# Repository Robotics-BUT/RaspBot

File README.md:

KAMBot Robotic platform
========================

This repository holds all development on RaspBot robotic project.

This repository is intended to be extended by students during their
work on semestral/bachelor and Diploma theses.

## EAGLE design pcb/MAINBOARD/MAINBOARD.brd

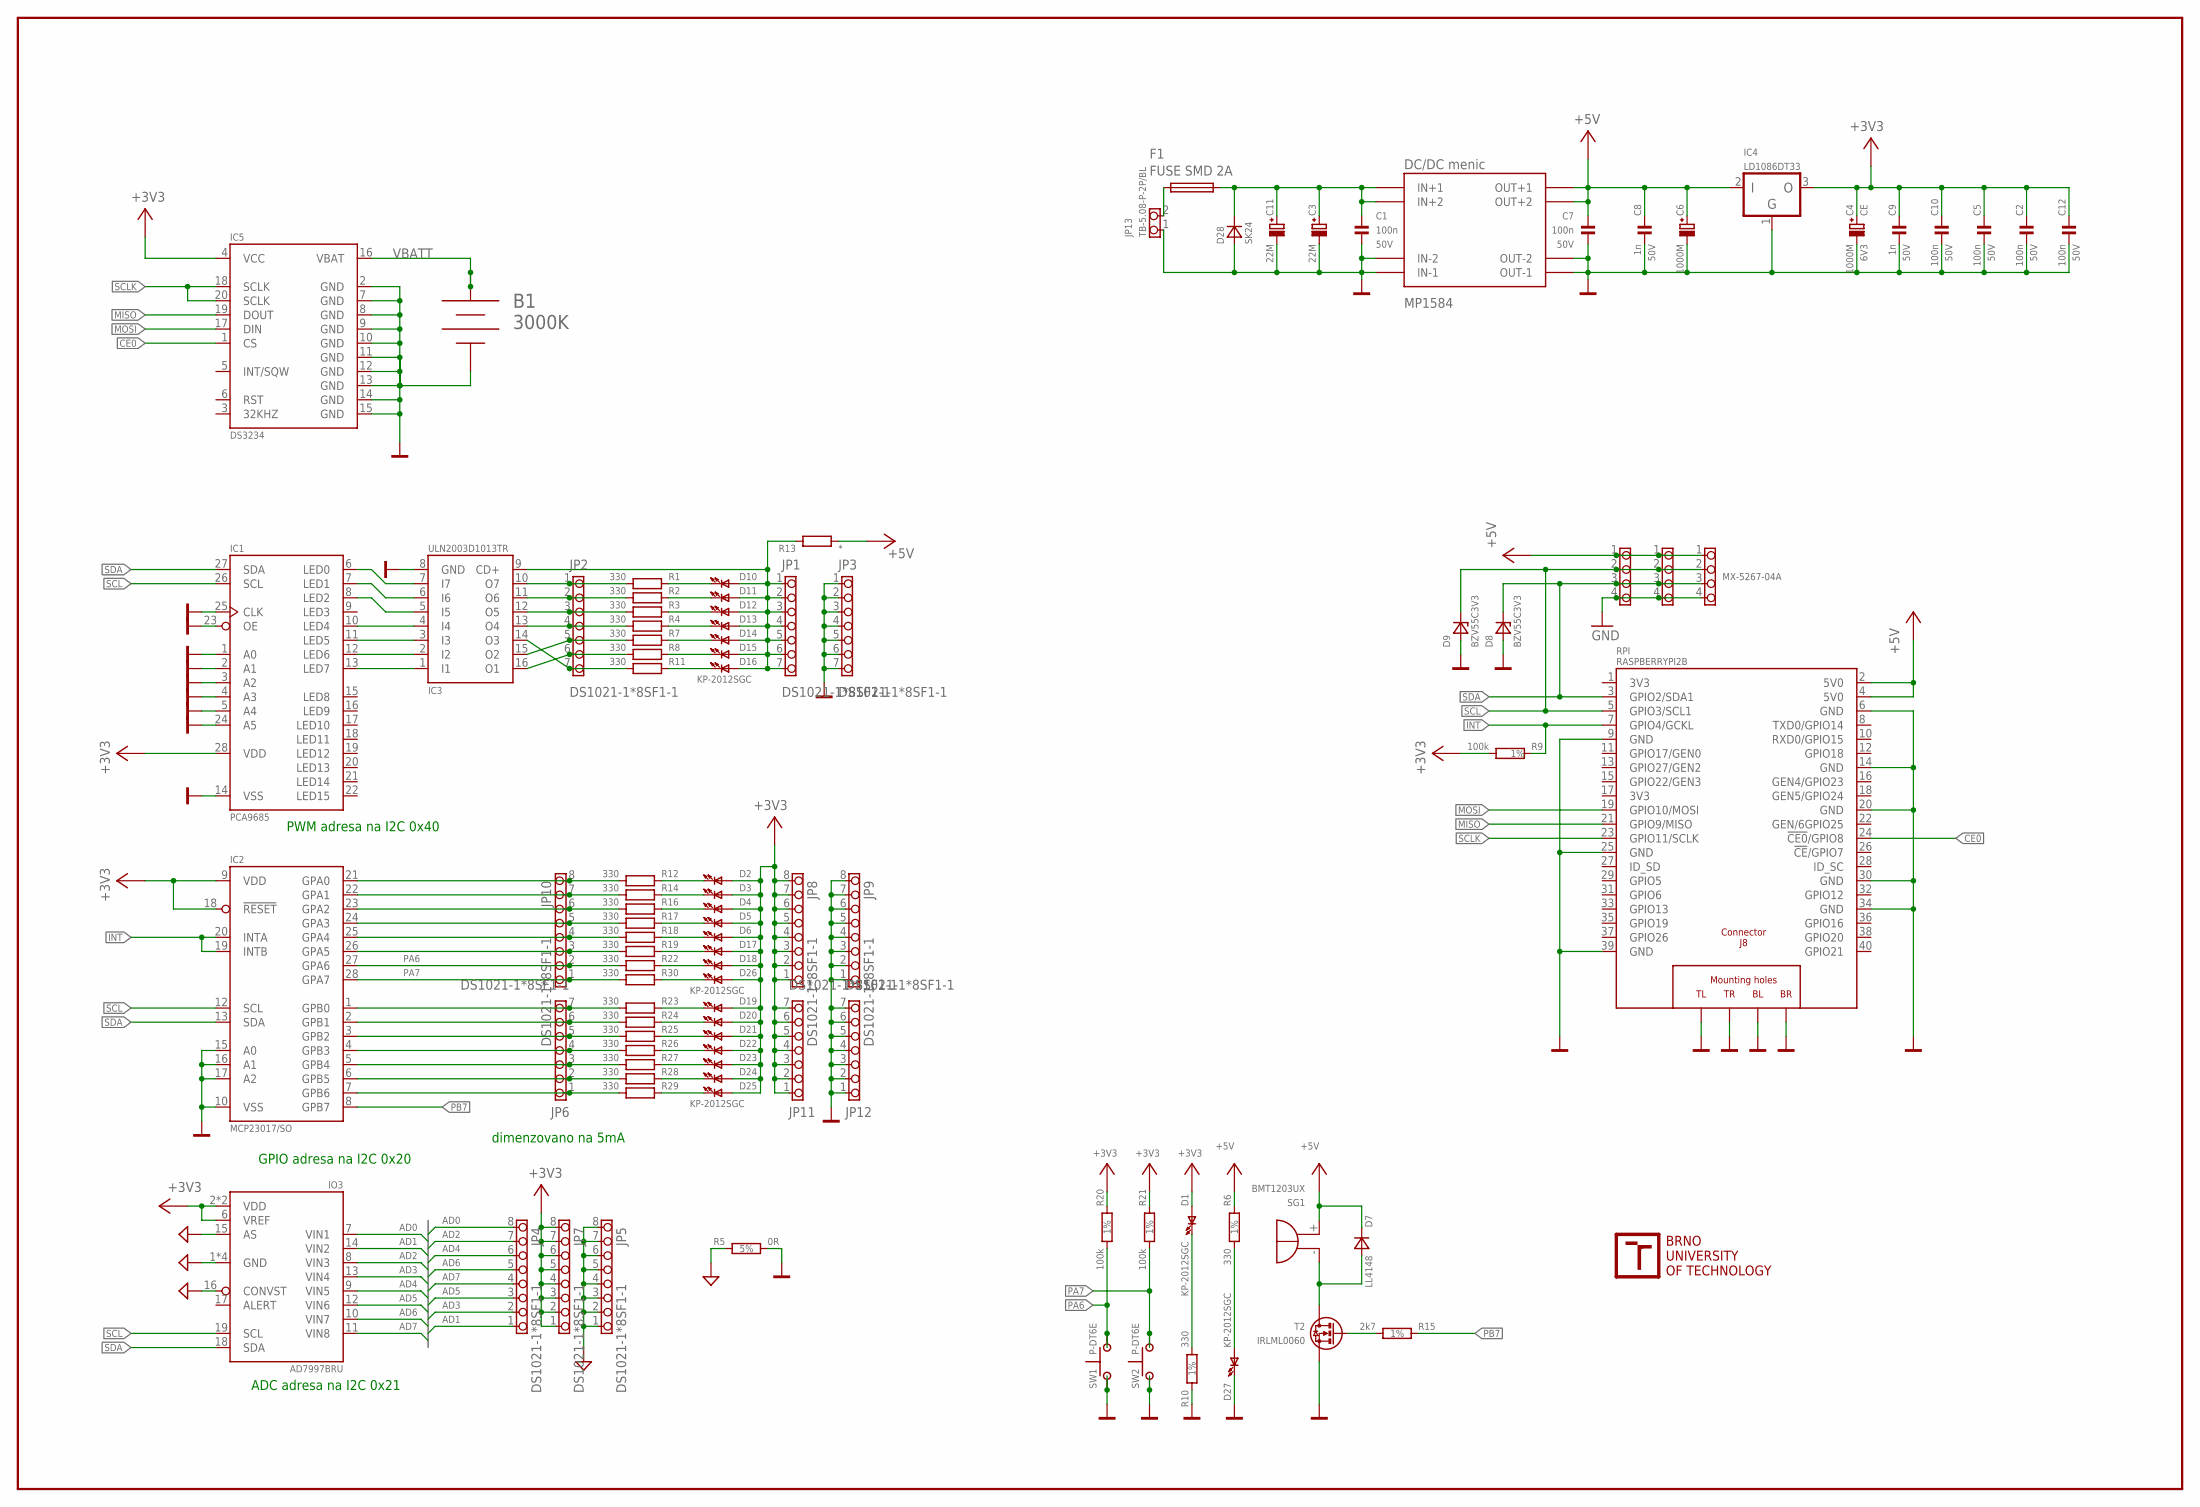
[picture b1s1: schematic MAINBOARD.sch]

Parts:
B1: 3000K
C1, C2, C5, C7, C10, C12: 100n; 0805; VOLTAGE 50V
C3, C11: 22M; CT7343D; VOLTAGE 25V
C4: 1000M; CE_D10L13_L; VOLTAGE 6V3
C6: 1000M; CE_D10L13_R; VOLTAGE 6V3
C8, C9: 1n; 0805; VOLTAGE 50V
D1, D2, D3, D4, D5, D6, D10, D11, D12, D13, D14, D15, D16, D17, D18, D19, D20, D21, D22, D23, D24, D25, D26, D27: KP-2012SGC; LED_0805
D7: LL4148; D_SOD80
D8, D9: BZV55C3V3; D_SOD80
D28: SK24; D_SMB
DC1: MP1584; DC-DC-STEP-DOWN-MALEJ
F1: FUSE SMD 2A; FUSE_SMD
IC1: PCA9685; TSSOP28
IC2: MCP23017/SO; SO28W
IC3: ULN2003D1013TR; SO16
IC4: LD1086DT33; TO252
IC5: DS3234; SO20W
IO3: AD7997BRU; TSSOP20
JP1, JP2, JP3, JP6, JP11, JP12: DS1021-1*8SF1-1; 1X07_254_M
JP4, JP5, JP7, JP8, JP9, JP10: DS1021-1*8SF1-1; 1X08_254_M
JP13: TB-5.08-P-2P/BL; 1X02_508_SROUB
JP19, JP25, JP26: MX-5267-04A; 1X04_250_MX5267
R1, R2, R3, R4, R7, R8, R11, R12, R14, R16, R17, R18, R19, R22, R23, R24, R25, R26, R27, R28, R29, R30: 330; 0805
R5: 0R; 1206; TOLERANCE 5%
R6, R10: 330; 0805; TOLERANCE 1%
R9, R20, R21: 100k; 0805; TOLERANCE 1%
R13: *; 0805
R15: 2k7; 0805; TOLERANCE 1%
RPI: RASPBERRYPI2B; RASPBERRYPI2
SG1: BMT1203UX; BMT1205XH7.5
SW1, SW2: P-DT6E; P-DTE6
T2: IRLML0060; SOT23

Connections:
+3V3: C2.1, C4.P (+), C5.1, C9.2, C10.2, C12.1, D1.A, D2.A, D3.A, D4.A, D5.A, D6.A, D17.A, D18.A, D19.A, D20.A, D21.A, D22.A, D23.A, D24.A, D25.A, D26.A, IC1.28 (VDD), IC2.9 (VDD), IC2.18 (!RESET), IC4.3 (OUT), IC5.4 (VCC), IO3.2 (VDD), IO3.5 (VDD), IO3.6 (VREF), JP7.1, JP7.2, JP7.3, JP7.4, JP7.5, JP7.6, JP7.7, JP7.8, JP8.1, JP8.2, JP8.3, JP8.4, JP8.5, JP8.6, JP8.7, JP8.8, JP11.1, JP11.2, JP11.3, JP11.4, JP11.5, JP11.6, JP11.7, R9.1, R20.2, R21.2
+5V: C6.P (+), C7.1, C8.1, D7.C (K), DC1.OUT1+ (OUT+1), DC1.OUT2+ (OUT+2), IC4.2 (IN), JP19.1, JP25.1, JP26.1, R6.2, R13.1, RPI.2 (5V0), RPI.4 (5V0), SG1.+
AD0: IO3.7 (VIN1), JP4.8
AD1: IO3.14 (VIN2), JP4.1
AD2: IO3.8 (VIN3), JP4.7
AD3: IO3.13 (VIN4), JP4.2
AD4: IO3.9 (VIN5), JP4.6
AD5: IO3.12 (VIN6), JP4.3
AD6: IO3.10 (VIN7), JP4.5
AD7: IO3.11 (VIN8), JP4.4
AGND: IO3.1 (GND), IO3.3 (GND), IO3.4 (GND), IO3.15 (AS), IO3.16 (CONVST), IO3.20 (GND), JP5.1, JP5.2, JP5.3, JP5.4, JP5.5, JP5.6, JP5.7, JP5.8, R5.2
B: R15.2, T2.1 (G)
C: D7.A, SG1.-, T2.2 (D)
CE0: IC5.1 (CS), RPI.24 (!CE0!/GPIO8)
GND: B1.-, C1.2, C2.2, C3.-, C4.M (-), C5.2, C6.M (-), C7.2, C8.2, C9.1, C10.1, C11.-, C12.2, D8.A, D9.A, D27.K (C), D28.A, DC1.IN1- (IN-1), DC1.IN2- (IN-2), DC1.OUT-1, DC1.OUT-2, IC1.1 (A0), IC1.2 (A1), IC1.3 (A2), IC1.4 (A3), IC1.5 (A4), IC1.14 (VSS), IC1.23 (OE), IC1.24 (A5), IC1.25 (CLK), IC2.10 (VSS), IC2.15 (A0), IC2.16 (A1), IC2.17 (A2), IC3.8 (GND), IC4.1 (GND), IC5.2 (GND), IC5.7 (GND), IC5.8 (GND), IC5.9 (GND), IC5.10 (GND), IC5.11 (GND), IC5.12 (GND), IC5.13 (GND), IC5.14 (GND), IC5.15 (GND), JP3.1, JP3.2, JP3.3, JP3.4, JP3.5, JP3.6, JP3.7, JP9.1, JP9.2, JP9.3, JP9.4, JP9.5, JP9.6, JP9.7, JP9.8, JP12.1, JP12.2, JP12.3, JP12.4, JP12.5, JP12.6, JP12.7, JP13.1, JP19.4, JP25.4, JP26.4, R5.1, R10.1, RPI.6 (GND), RPI.9 (GND), RPI.14 (GND), RPI.20 (GND), RPI.25 (GND), RPI.30 (GND), RPI.34 (GND), RPI.39 (GND), RPI.PE_BL (BL), RPI.PE_BR (BR), RPI.PE_TL (TL), RPI.PE_TR (TR), SW1.1, SW1.1A (3), SW2.1, SW2.1A (3), T2.3 (S)
INT: IC2.19 (INTB), IC2.20 (INTA), R9.2, RPI.7 (GPIO4/GCKL)
LED0: IC1.6 (LED0), IC3.7 (I7)
MISO: IC5.19 (DOUT), RPI.21 (GPIO9/MISO)
MOSI: IC5.17 (DIN), RPI.19 (GPIO10/MOSI)
unnamed: D26.K (C), R30.2
unnamed: D2.K (C), R12.2
unnamed: D18.K (C), R22.2
unnamed: D17.K (C), R19.2
unnamed: D6.K (C), R18.2
unnamed: D27.A, R6.1
unnamed: C1.1, C3.+, C11.+, D28.K, DC1.IN+1, DC1.IN+2, F1.2
unnamed: F1.1, JP13.2
unnamed: IC1.7 (LED1), IC3.6 (I6)
unnamed: D10.A, D11.A, D12.A, D13.A, D14.A, D15.A, D16.A, IC3.9 (CD+), JP1.1, JP1.2, JP1.3, JP1.4, JP1.5, JP1.6, JP1.7, R13.2
unnamed: IC1.8 (LED2), IC3.5 (I5)
unnamed: D10.K (C), R1.2
unnamed: D16.K (C), R11.2
unnamed: D1.K (C), R10.2
unnamed: IC1.10 (LED4), IC3.4 (I4)
unnamed: IC1.11 (LED5), IC3.3 (I3)
unnamed: IC1.12 (LED6), IC3.2 (I2)
unnamed: IC1.13 (LED7), IC3.1 (I1)
unnamed: D15.K (C), R8.2
unnamed: D14.K (C), R7.2
unnamed: D13.K (C), R4.2
unnamed: D12.K (C), R3.2
unnamed: D11.K (C), R2.2
unnamed: D5.K (C), R17.2
unnamed: D4.K (C), R16.2
unnamed: D3.K (C), R14.2
unnamed: D19.K (C), R23.2
unnamed: D25.K (C), R29.2
unnamed: D24.K (C), R28.2
unnamed: D23.K (C), R27.2
unnamed: D22.K (C), R26.2
unnamed: D21.K (C), R25.2
unnamed: D20.K (C), R24.2
PA0: IC2.21 (GPA0), JP10.8, R12.1
PA1: IC2.22 (GPA1), JP10.7, R14.1
PA2: IC2.23 (GPA2), JP10.6, R16.1
PA3: IC2.24 (GPA3), JP10.5, R17.1
PA4: IC2.25 (GPA4), JP10.4, R18.1
PA5: IC2.26 (GPA5), JP10.3, R19.1
PA6: IC2.27 (GPA6), JP10.2, R20.1, R22.1, SW1.2, SW1.2A (4)
PA7: IC2.28 (GPA7), JP10.1, R21.1, R30.1, SW2.2, SW2.2A (4)
PB0: IC2.1 (GPB0), JP6.7, R23.1
PB1: IC2.2 (GPB1), JP6.6, R24.1
PB2: IC2.3 (GPB2), JP6.5, R25.1
PB3: IC2.4 (GPB3), JP6.4, R26.1
PB4: IC2.5 (GPB4), JP6.3, R27.1
PB5: IC2.6 (GPB5), JP6.2, R28.1
PB6: IC2.7 (GPB6), JP6.1, R29.1
PB7: IC2.8 (GPB7), R15.1
PWM0: IC3.10 (O7), JP2.1, R1.1
PWM1: IC3.11 (O6), JP2.2, R2.1
PWM2: IC3.12 (O5), JP2.3, R3.1
PWM4: IC3.13 (O4), JP2.4, R4.1
PWM5: IC3.14 (O3), JP2.7, R11.1
PWM6: IC3.15 (O2), JP2.5, R7.1
PWM7: IC3.16 (O1), JP2.6, R8.1
SCL: D9.C (K), IC1.26 (SCL), IC2.12 (SCL), IO3.19 (SCL), JP19.2, JP25.2, JP26.2, RPI.5 (GPIO3/SCL1)
SCLK: IC5.18 (SCLK), IC5.20 (SCLK), RPI.23 (GPIO11/SCLK)
SDA: D8.C (K), IC1.27 (SDA), IC2.13 (SDA), IO3.18 (SDA), JP19.3, JP25.3, JP26.3, RPI.3 (GPIO2/SDA1)
VBATT: B1.+, B1.++, IC5.16 (VBAT)

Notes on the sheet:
GPIO adresa na I2C 0x20
dimenzovano na 5mA
PWM adresa na I2C 0x40
ADC adresa na I2C 0x21

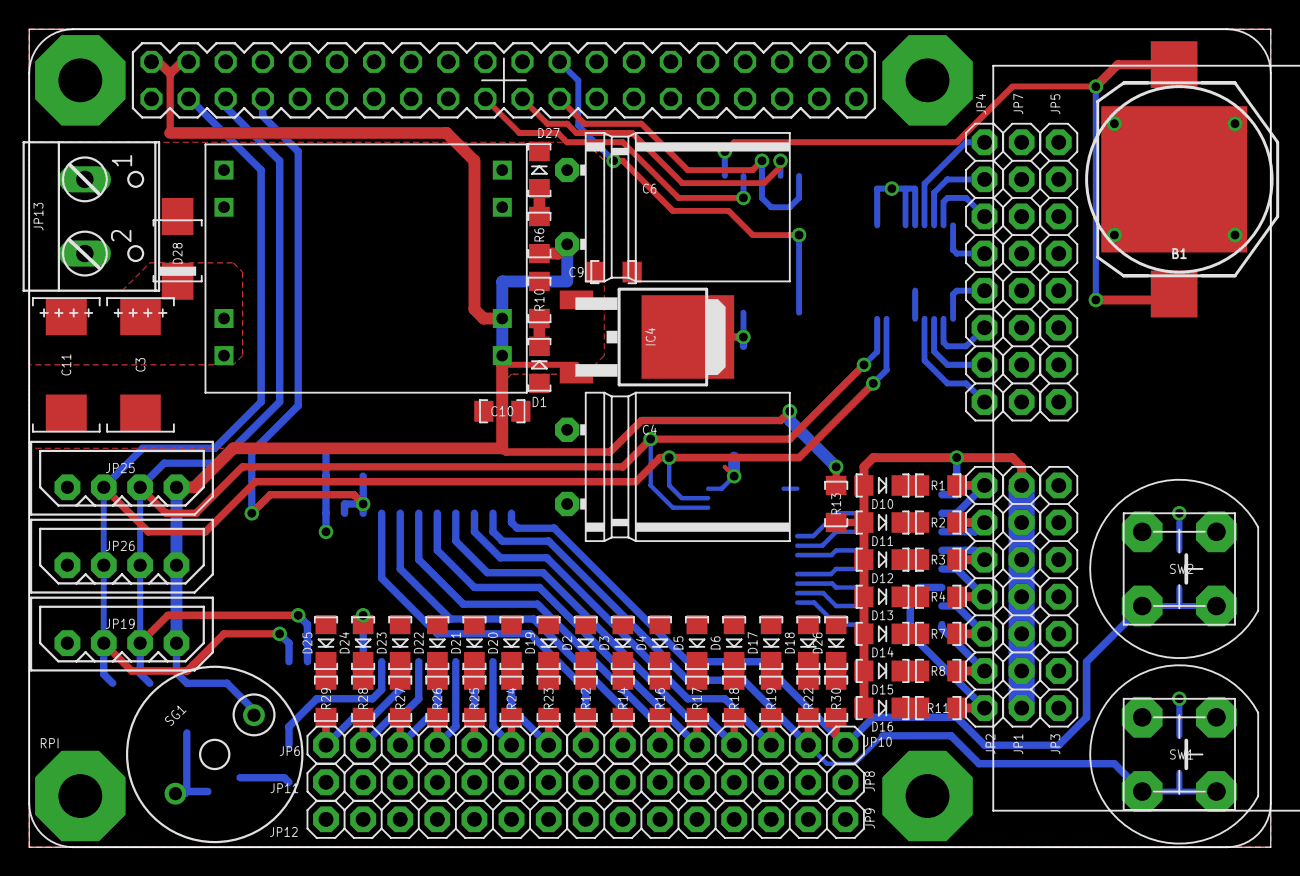
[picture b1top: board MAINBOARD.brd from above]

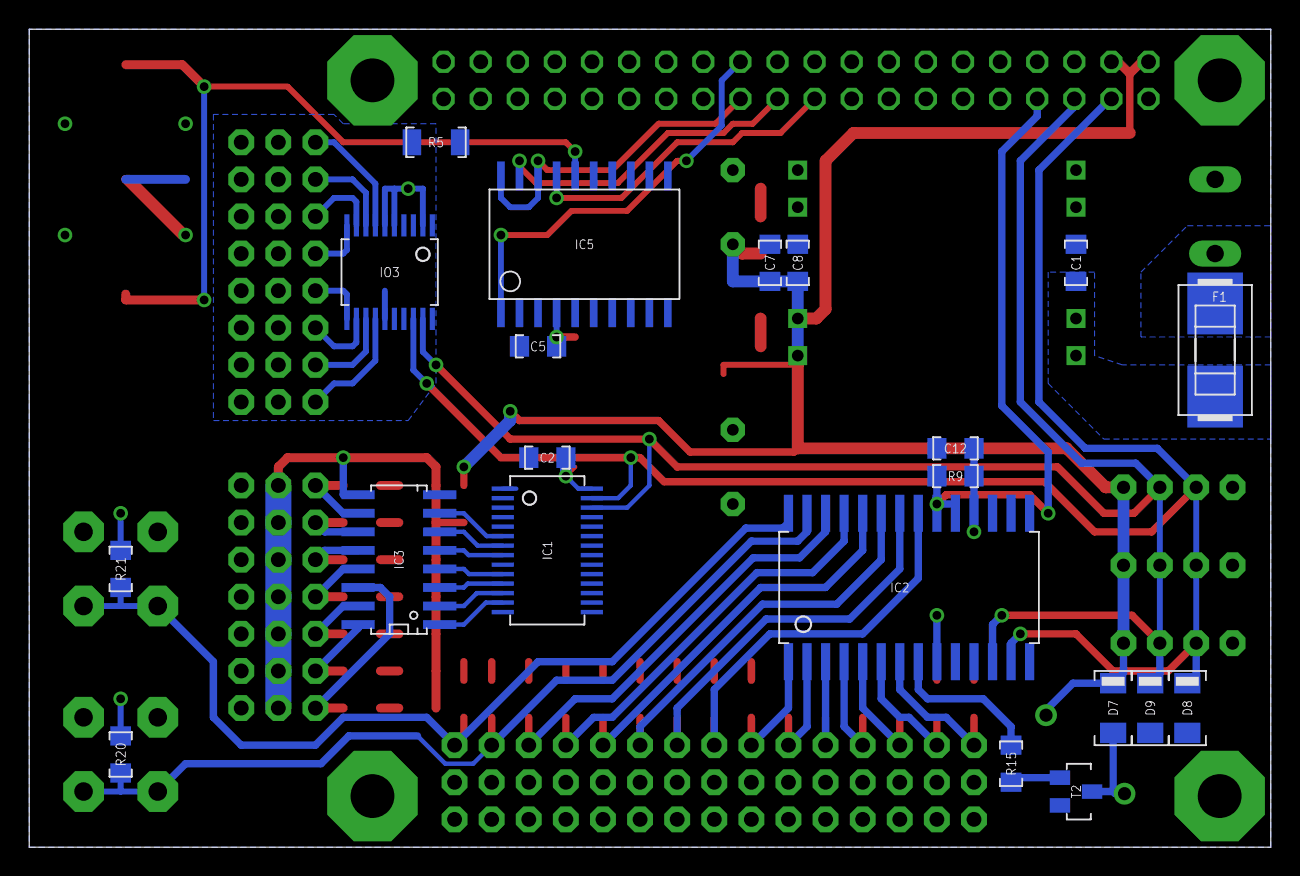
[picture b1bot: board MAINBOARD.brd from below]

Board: 2 copper layers, 85.0 x 56.0 mm, 103 parts (21 on the bottom side), 79 nets.

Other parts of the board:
U$2: DIN_A4_1:2
U$3: RAZITKO_1:2
U$4: VUT_LOGO

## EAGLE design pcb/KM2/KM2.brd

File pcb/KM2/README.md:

Modul ovladace dvou krokovych motoru
====================================

Tento modul ma za ukol v realnem case ovladat dva krokove motory dle instrukci,
ktere dostane od ridiciho procesoru (Raspberry nebo jiny). Pri preruseni toku dat
po sbernici musi modul zastavit motory.

Varianta ovladani proudu do motoru, rizeni vykonu motoru podle pozadovane rychlosti kvuli otepleni motoru.

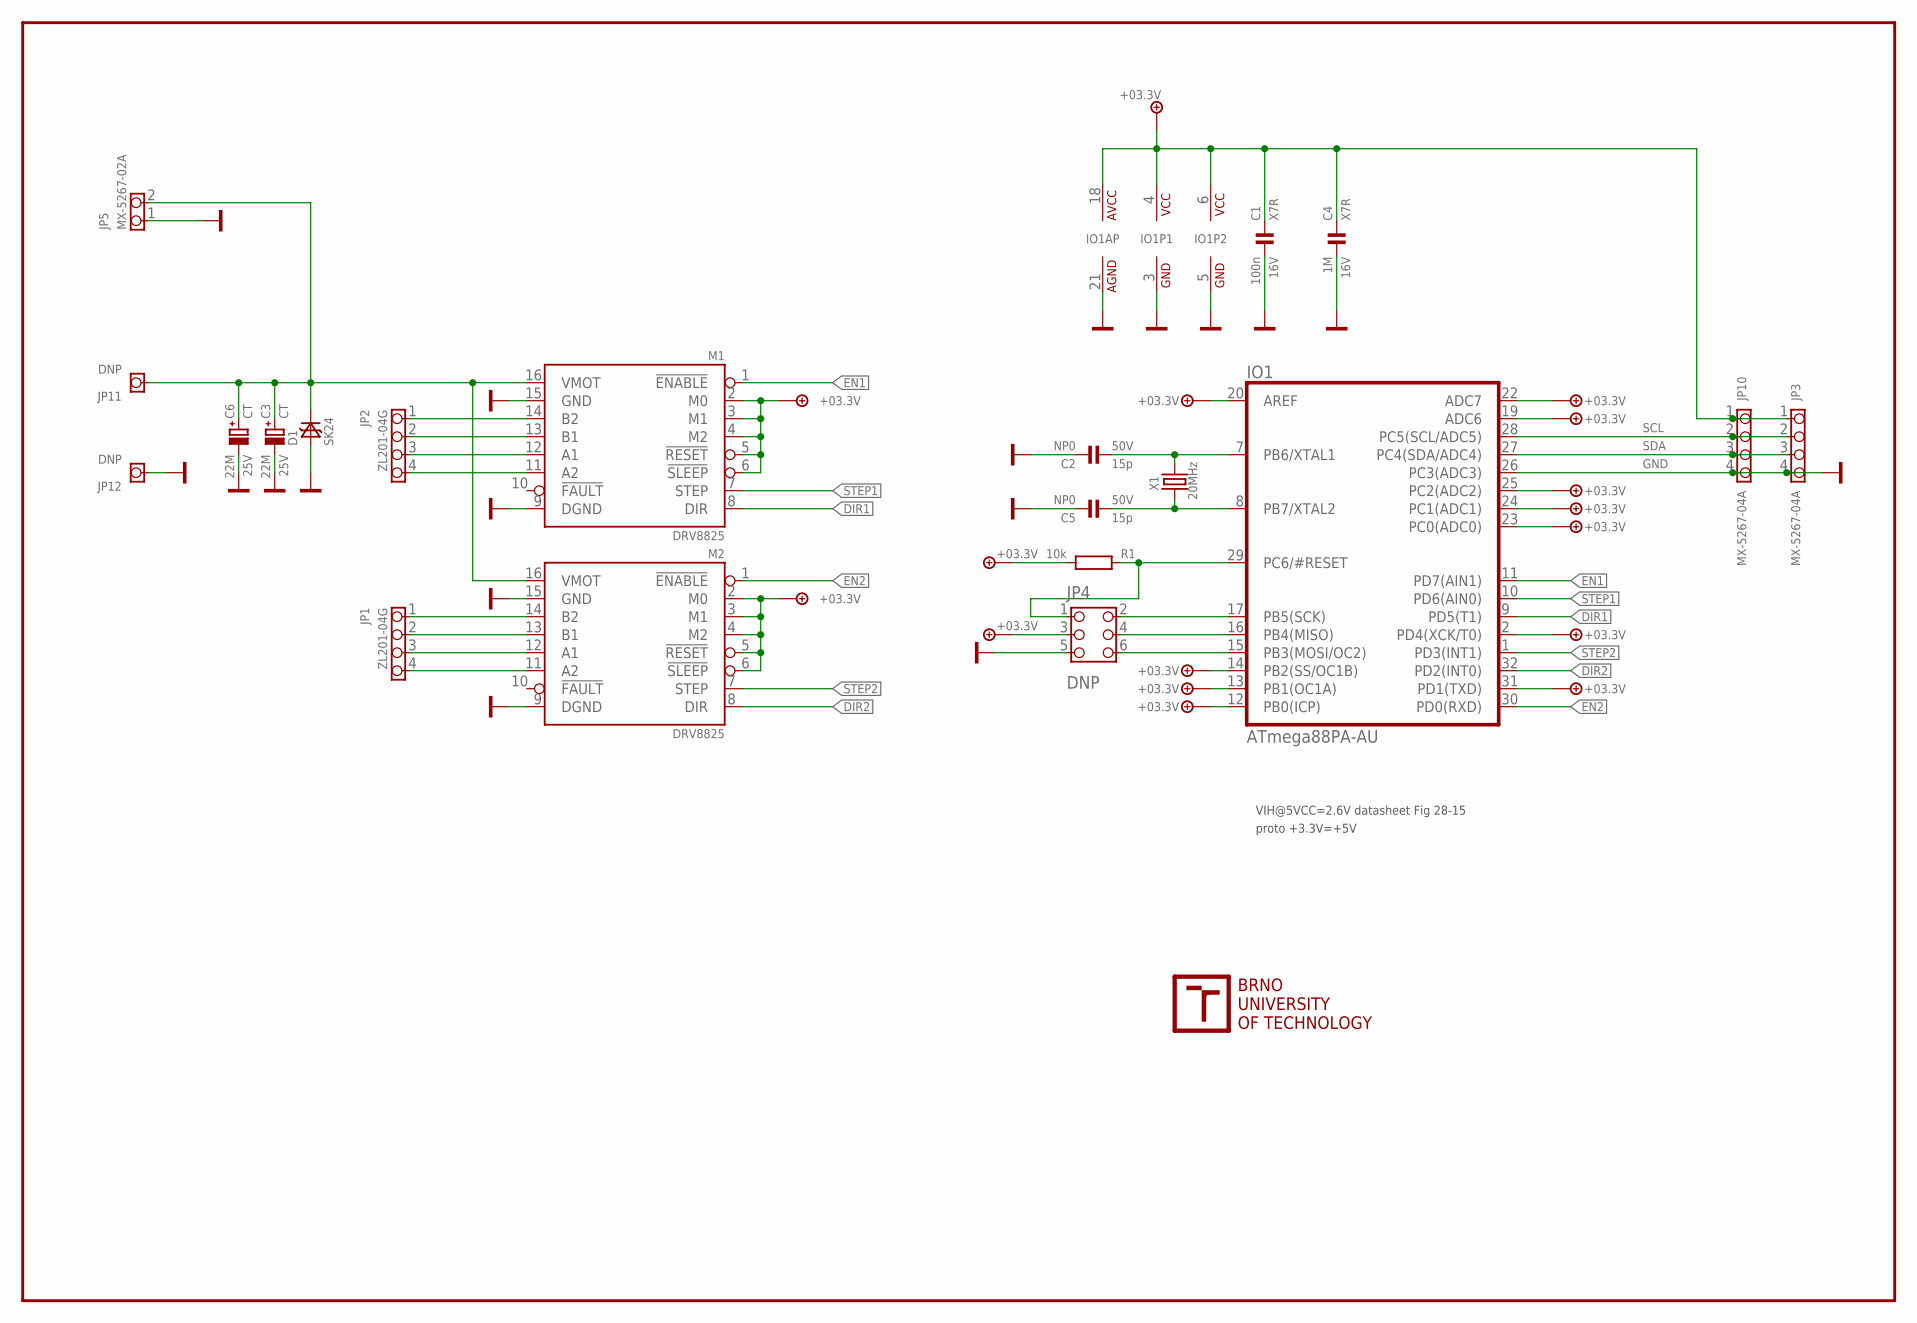
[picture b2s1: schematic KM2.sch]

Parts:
C1: 100n; 0805; VOLTAGE 16V
C2, C5: 15p; 0805; VOLTAGE 50V
C3, C6: 22M; CT7343D; VOLTAGE 25V
C4: 1M; 0805; VOLTAGE 16V
D1: SK24; D_SMB
IO1: ATmega88PA-AU; TQFP32
JP1, JP2: ZL201-04G; 1X04_254_MH
JP3, JP10: MX-5267-04A; 1X04_250_MX5267
JP4: DNP; 2X03_254_FP
JP5: MX-5267-02A; 1X02_250_MX5267
JP11, JP12: DNP; 1X01_254_254_PAD
M1, M2: DRV8825; MODULE_16P
R1: 10k; 0805
X1: 20MHz; X_HC49/S

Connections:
+3.3V: C1.1, C4.1, IO1.2 (PD4(XCK/T0)), IO1.4 (VCC), IO1.6 (VCC), IO1.12 (PB0(ICP)), IO1.13 (PB1(OC1A)), IO1.14 (PB2(SS/OC1B)), IO1.18 (VCC), IO1.19 (ADC6), IO1.20 (AREF), IO1.22 (ADC7), IO1.23 (PC0(ADC0)), IO1.24 (PC1(ADC1)), IO1.25 (PC2(ADC2)), IO1.31 (PD1(TXD)), JP3.1, JP4.3, JP10.1, M1.2 (M0), M1.3 (M1), M1.4 (M2), M1.5 (!RESET), M1.6 (!SLEEP), M2.2 (M0), M2.3 (M1), M2.4 (M2), M2.5 (!RESET), M2.6 (!SLEEP), R1.1
DIR1: IO1.9 (PD5(T1)), M1.8 (DIR)
DIR2: IO1.32 (PD2(INT0)), M2.8 (DIR)
EN1: IO1.11 (PD7(AIN1)), M1.1 (!ENABLE)
EN2: IO1.30 (PD0(RXD)), M2.1 (!ENABLE)
GND: C1.2, C2.1, C3.-, C4.2, C5.1, C6.-, D1.A, IO1.3 (GND), IO1.5 (GND), IO1.21 (GND), IO1.26 (PC3(ADC3)), JP3.4, JP4.5, JP5.1, JP10.4, JP12.P$1, M1.9 (DGND), M1.15 (GND), M2.9 (DGND), M2.15 (GND)
unnamed: JP1.1, M2.14 (B2)
unnamed: JP1.2, M2.13 (B1)
unnamed: JP1.3, M2.12 (A1)
unnamed: JP1.4, M2.11 (A2)
unnamed: JP2.1, M1.14 (B2)
unnamed: JP2.2, M1.13 (B1)
unnamed: JP2.3, M1.12 (A1)
unnamed: JP2.4, M1.11 (A2)
unnamed: C2.2, IO1.7 (PB6/XTAL1), X1.2
unnamed: C5.2, IO1.8 (PB7/XTAL2), X1.1
unnamed: IO1.17 (PB5(SCK)), JP4.2
unnamed: IO1.16 (PB4(MISO)), JP4.4
unnamed: IO1.15 (PB3(MOSI/OC2)), JP4.6
unnamed: IO1.29 (PC6/#RESET), JP4.1, R1.2
SCL: IO1.28 (PC5(SCL/ADC5)), JP3.2, JP10.2
SDA: IO1.27 (PC4(SDA/ADC4)), JP3.3, JP10.3
STEP1: IO1.10 (PD6(AIN0)), M1.7 (STEP)
STEP2: IO1.1 (PD3(INT1)), M2.7 (STEP)
VBAT+: C3.+, C6.+, D1.K, JP5.2, JP11.P$1, M1.16 (VMOT), M2.16 (VMOT)

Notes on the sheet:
VIH@5VCC=2.6V datasheet Fig 28-15
proto +3.3V=+5V

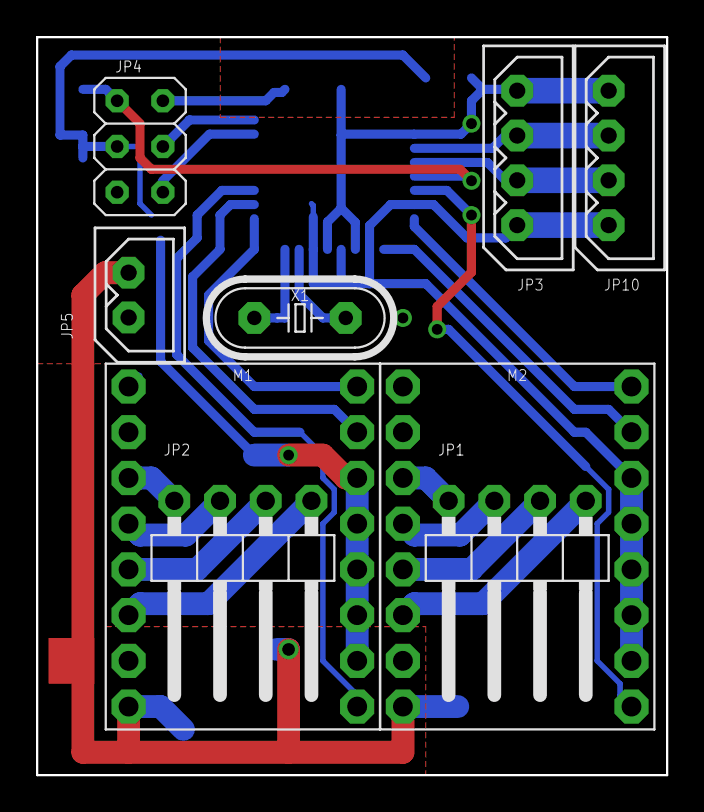
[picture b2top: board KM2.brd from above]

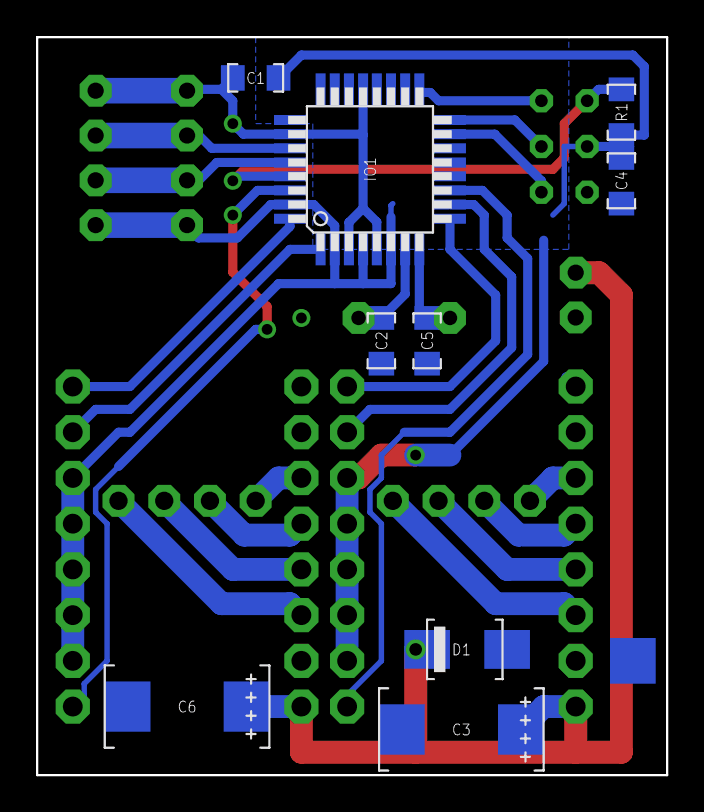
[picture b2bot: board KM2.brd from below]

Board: 2 copper layers, 35.0 x 41.0 mm, 23 parts (10 on the bottom side), 25 nets.

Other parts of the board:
U$1: DIN_A4_1:2
U$2: RAZITKO_1:2
U$3: VUT_LOGO

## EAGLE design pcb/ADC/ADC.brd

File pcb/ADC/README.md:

Modul A/D prevodniku s AD7997
=============================

Modul ma za ukol prevadet analogova napeti v rozsahu 0-3.3V

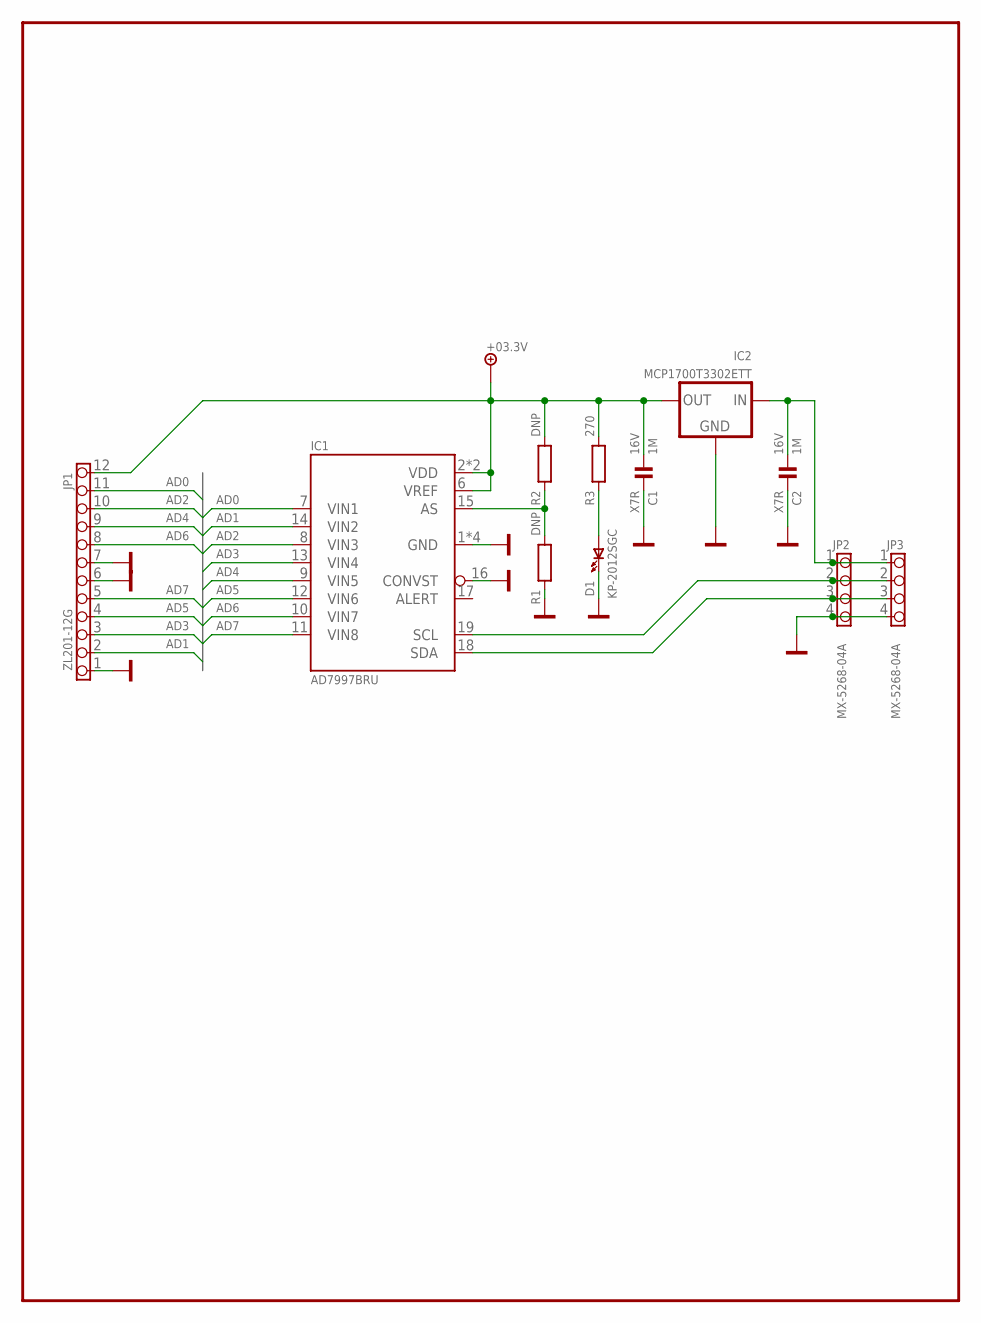
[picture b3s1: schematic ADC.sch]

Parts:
C1, C2: 1M; 0805; VOLTAGE 16V
D1: KP-2012SGC; LED_0805
IC1: AD7997BRU; TSSOP20
IC2: MCP1700T3302ETT; SOT23
JP1: ZL201-12G; 1X12_254_EDGE
JP2, JP3: MX-5268-04A; 1X04_250_MX5268
R1, R2: DNP; 0805
R3: 270; 0805

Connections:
+3.3V: C1.2, IC1.2 (VDD), IC1.5 (VDD), IC1.6 (VREF), IC2.2 (OUT), JP1.12, R2.2, R3.2
AD0: IC1.7 (VIN1), JP1.11
AD1: IC1.14 (VIN2), JP1.2
AD2: IC1.8 (VIN3), JP1.10
AD3: IC1.13 (VIN4), JP1.3
AD4: IC1.9 (VIN5), JP1.9
AD5: IC1.12 (VIN6), JP1.4
AD6: IC1.10 (VIN7), JP1.8
AD7: IC1.11 (VIN8), JP1.5
GND: C1.1, C2.1, D1.K (C), IC1.1 (GND), IC1.3 (GND), IC1.4 (GND), IC1.16 (CONVST), IC1.20 (GND), IC2.1 (GND), JP1.1, JP1.6, JP1.7, JP2.4, JP3.4, R1.2
unnamed: C2.2, IC2.3 (IN), JP2.1, JP3.1
unnamed: IC1.19 (SCL), JP2.2, JP3.2
unnamed: IC1.18 (SDA), JP2.3, JP3.3
unnamed: D1.A, R3.1
unnamed: IC1.15 (AS), R1.1, R2.1

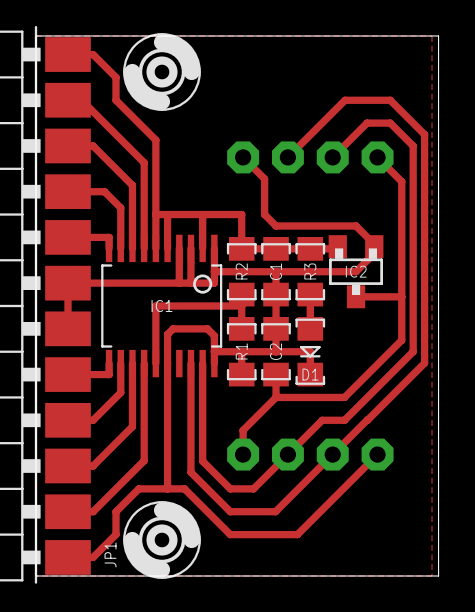
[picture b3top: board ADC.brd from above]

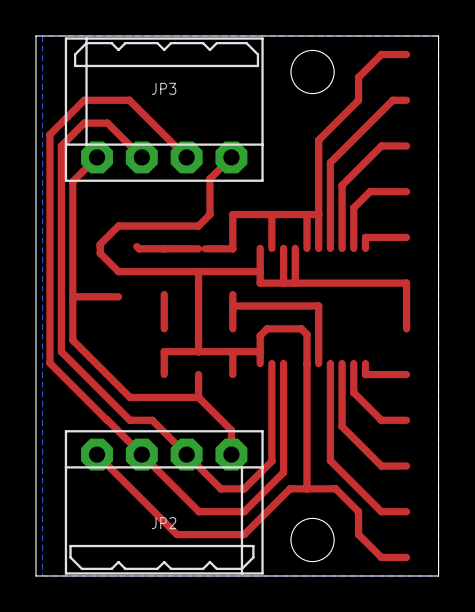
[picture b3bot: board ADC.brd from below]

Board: 2 copper layers, 22.4 x 30.0 mm, 15 parts (2 on the bottom side), 15 nets.

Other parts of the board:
H1, H2: 2,4
U$2: DIN_A4_SCALE4
U$3: DIN_DOCFIELD_SCALE4

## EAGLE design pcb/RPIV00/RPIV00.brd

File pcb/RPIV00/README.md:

Elektronika RPIv00
==================

Tato elektronika je prvni verze dps, ktera se nasadila na RaspberryPi. Zajistuje
napajeni pro Raspberry z 12V baterie, a obsahuje menice pro dva krokove motory,
buzene primo z Raspberry Pi.

Chyby
-----

V teto verzi je plno chyb, zejmena pin ENABLE u obou driveru krokovych motoru 
musi byt skrabnutim spoje odpojen od napajeni a pripojen dratovou spojkou na
piny raspberry (viz RaspBot.h)

POZOR
-----

Tato verze rizeni nebude dale podporovana, prechazi se na rizeni pres I2C s
modulem KM2. Je zde uvedena jen pro doplneni dokumentace.

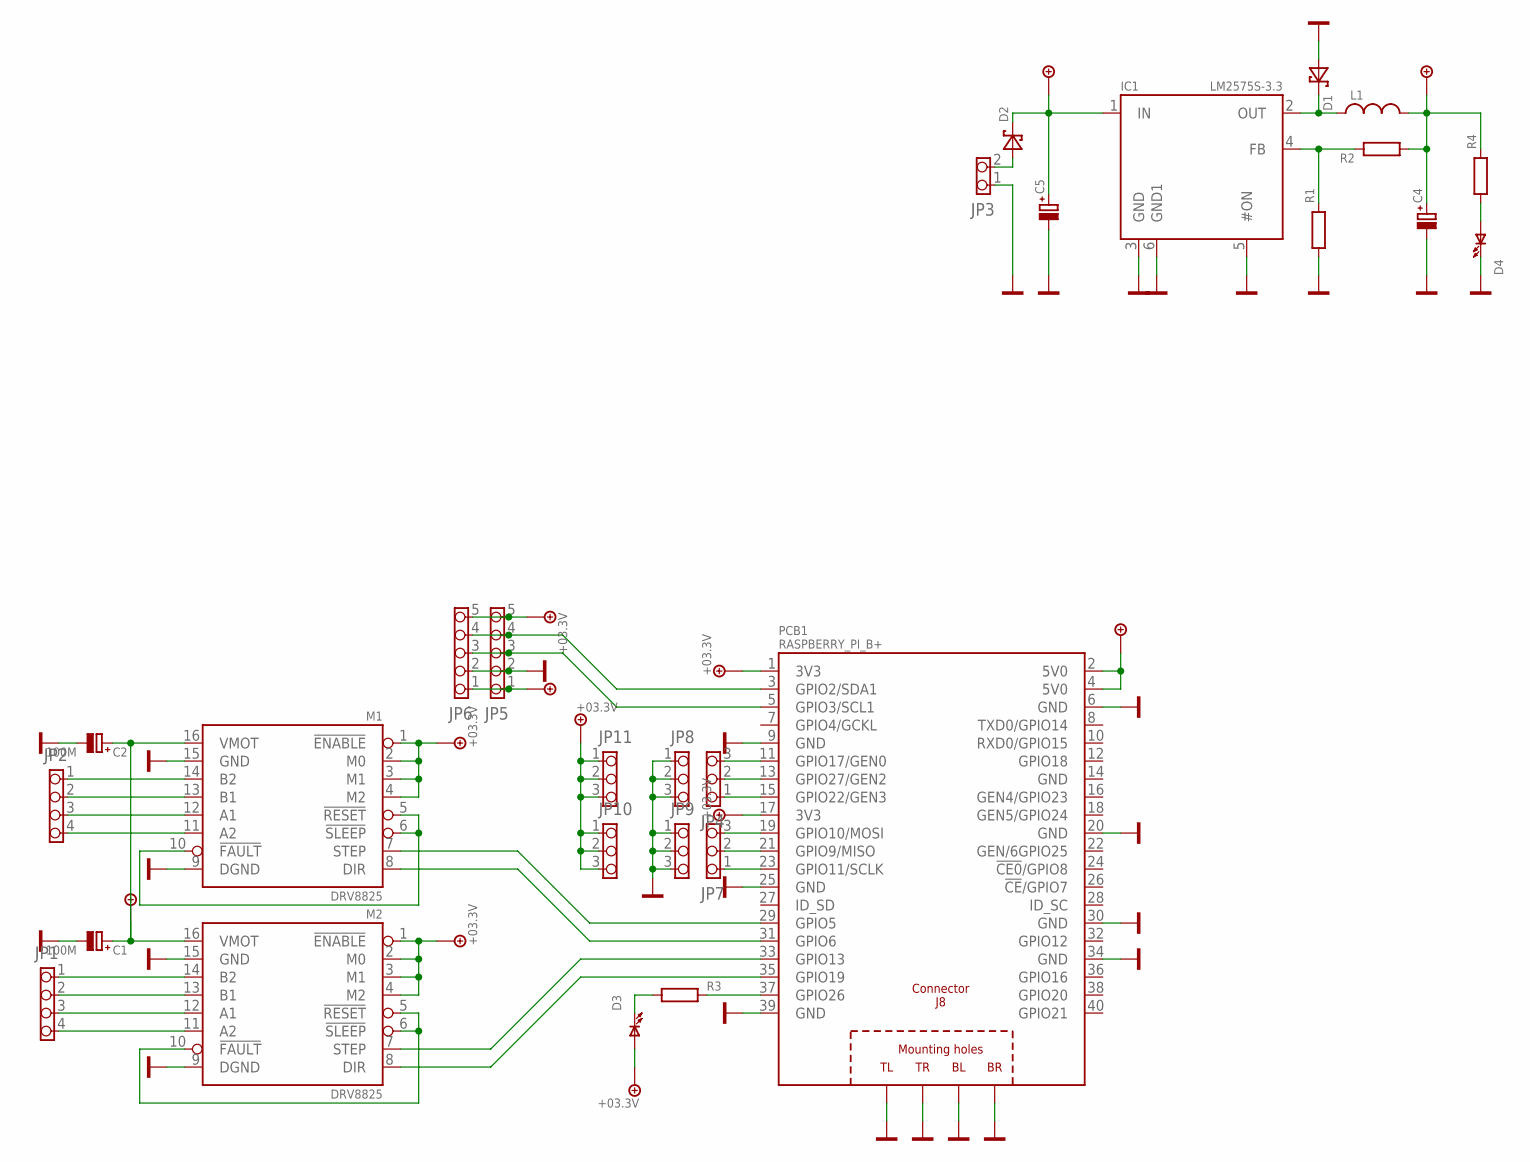
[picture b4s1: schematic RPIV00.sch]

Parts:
C1, C2: 100M; CE_D10L13_L
C4: CE_D10L13_L
C5: CE_D10L13_R
D1, D2: D_SCHOTKY_SMB; D_SMB
D3, D4: LED0805; LED_0805
IC1: LM2575S-3.3; TO263-5
JP1, JP2: PINHD-1X4; 1X04_254_M
JP3: PINHD-1X2_508_V; 1X02_508_V
JP4, JP7, JP8, JP9, JP10, JP11: PINHD-1X3; 1X03_254_M
JP5, JP6: PINHD-1X5; 1X05_254_M
L1: L_DE1207; DE1207
M1, M2: DRV8825; MODULE_16P
PCB1: RASPBERRY_PI_B+
R1, R2, R3, R4: R_R0805; 0805

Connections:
+3.3V: D3.A, JP5.5, JP6.5, JP10.1, JP10.2, JP10.3, JP11.1, JP11.2, JP11.3, M1.1 (!ENABLE), M1.2 (M0), M1.3 (M1), M1.4 (M2), M2.1 (!ENABLE), M2.2 (M0), M2.3 (M1), M2.4 (M2), PCB1.1 (3V3), PCB1.17 (3V3)
+5V: C4.P (+), JP5.1, JP6.1, L1.1, PCB1.2 (5V0), PCB1.4 (5V0), R2.1, R4.2
+24V: C1.P (+), C2.P (+), C5.P (+), D2.K, IC1.1 (IN), M1.16 (VMOT), M2.16 (VMOT)
GND: C1.M (-), C2.M (-), C4.M (-), C5.M (-), D1.A, D4.K (C), IC1.3 (GND), IC1.5 (#ON), IC1.6 (GND1), JP3.1, JP5.2, JP6.2, JP8.1, JP8.2, JP8.3, JP9.1, JP9.2, JP9.3, M1.9 (DGND), M1.15 (GND), M2.9 (DGND), M2.15 (GND), PCB1.6 (GND), PCB1.9 (GND), PCB1.20 (GND), PCB1.25 (GND), PCB1.30 (GND), PCB1.34 (GND), PCB1.39 (GND), PCB1.PE_BL (BL), PCB1.PE_BR (BR), PCB1.PE_TL (TL), PCB1.PE_TR (TR), R1.1
unnamed: JP1.1, M2.14 (B2)
unnamed: JP1.2, M2.13 (B1)
unnamed: JP1.3, M2.12 (A1)
unnamed: JP1.4, M2.11 (A2)
unnamed: JP2.1, M1.14 (B2)
unnamed: JP2.2, M1.13 (B1)
unnamed: JP2.3, M1.12 (A1)
unnamed: JP2.4, M1.11 (A2)
unnamed: JP4.3, PCB1.11 (GPIO17/GEN0)
unnamed: M2.8 (DIR), PCB1.35 (GPIO19)
unnamed: M2.7 (STEP), PCB1.33 (GPIO13)
unnamed: M1.8 (DIR), PCB1.31 (GPIO6)
unnamed: M1.7 (STEP), PCB1.29 (GPIO5)
unnamed: JP4.2, PCB1.13 (GPIO27/GEN2)
unnamed: M2.5 (!RESET), M2.6 (!SLEEP), M2.10 (!FAULT)
unnamed: M1.5 (!RESET), M1.6 (!SLEEP), M1.10 (!FAULT)
unnamed: JP4.1, PCB1.15 (GPIO22/GEN3)
unnamed: JP7.3, PCB1.19 (GPIO10/MOSI)
unnamed: JP7.2, PCB1.21 (GPIO9/MISO)
unnamed: D1.K, IC1.2 (OUT), L1.2
unnamed: IC1.4 (FB), R1.2, R2.2
unnamed: D2.A, JP3.2
unnamed: JP7.1, PCB1.23 (GPIO11/SCLK)
unnamed: PCB1.37 (GPIO26), R3.2
unnamed: D3.K (C), R3.1
unnamed: D4.A, R4.1
SCL: JP5.3, JP6.3, PCB1.5 (GPIO3/SCL1)
SDA: JP5.4, JP6.4, PCB1.3 (GPIO2/SDA1)

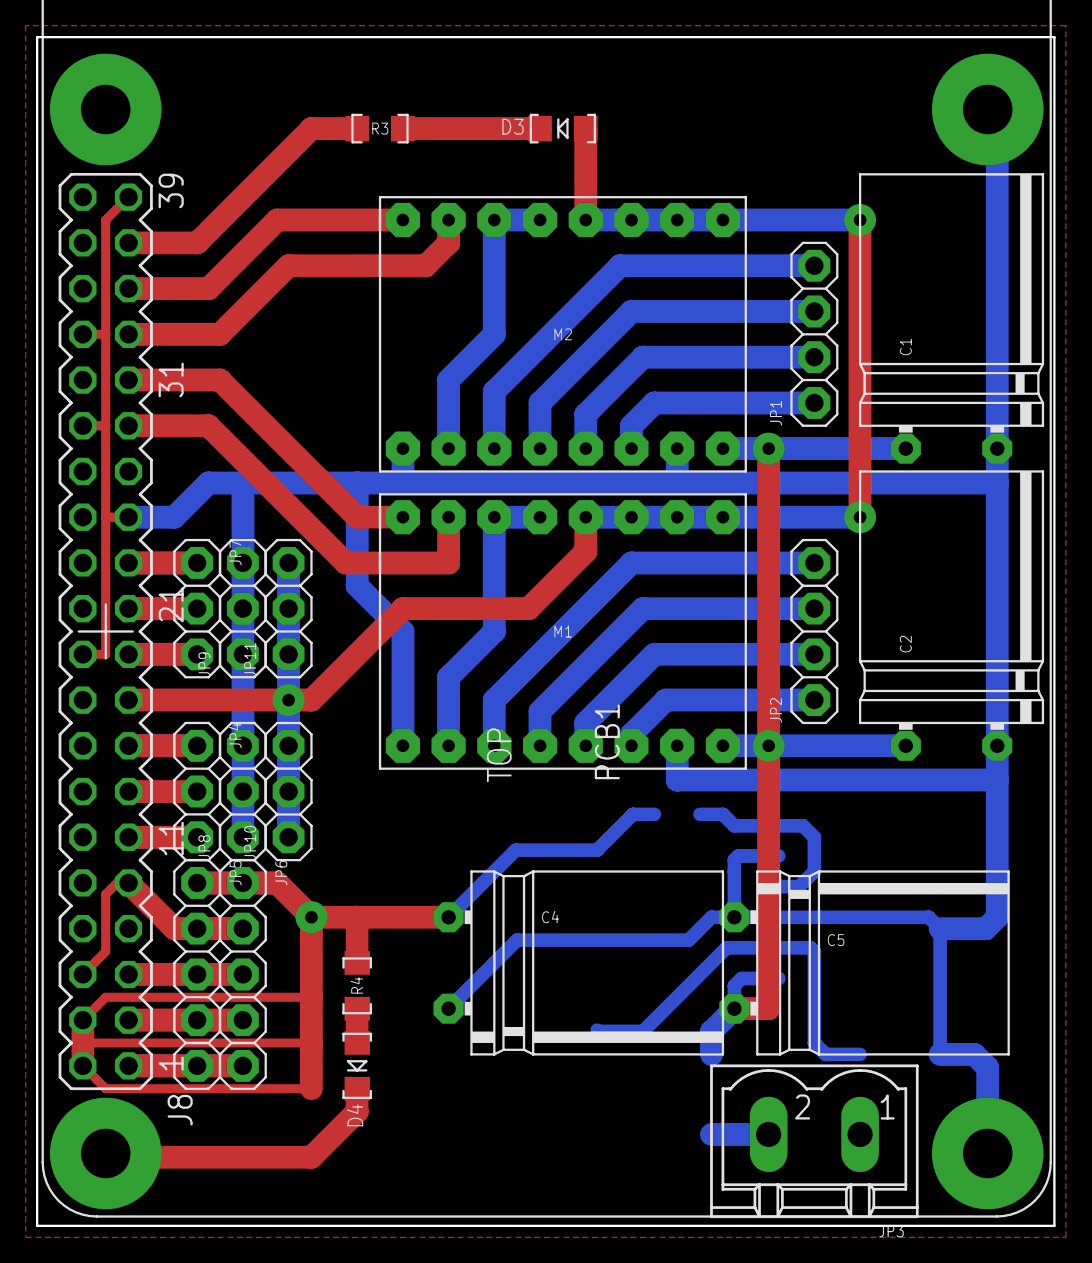
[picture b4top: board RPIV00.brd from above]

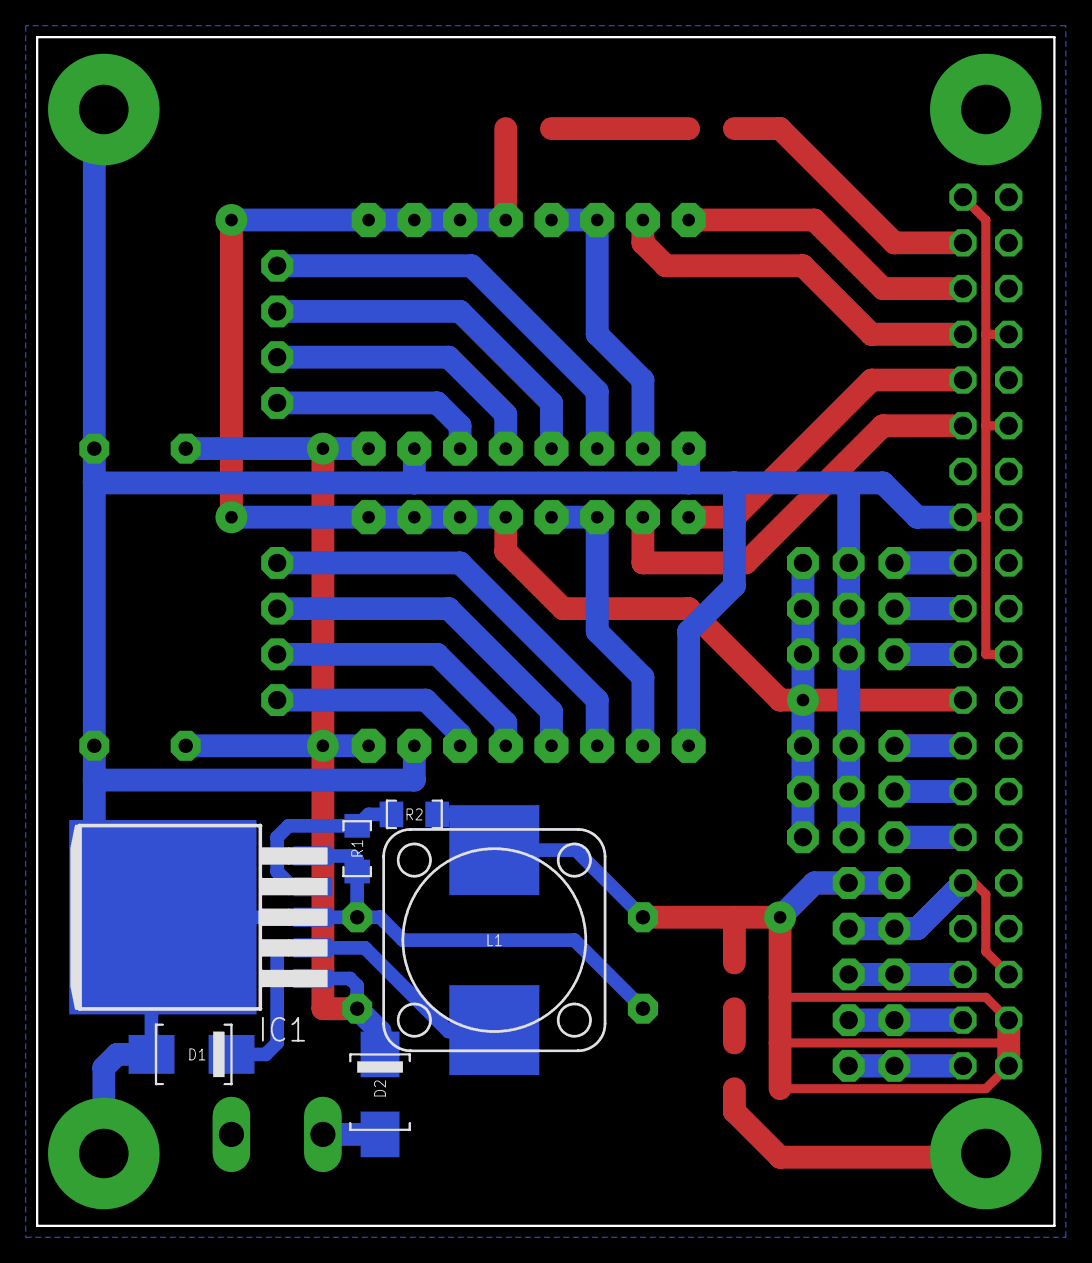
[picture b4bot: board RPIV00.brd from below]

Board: 2 copper layers, 56.5 x 66.0 mm, 28 parts (6 on the bottom side), 32 nets.

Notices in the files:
parts and their libraries:
Copyright (C) PaJa 2011
